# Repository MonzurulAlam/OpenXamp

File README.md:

# OpenExoAmp
Bio-signal Amplifier

### OBJECTIVES:
<P align="justify"> The objective of this project is to develop a bio-signal amplifier for sensing physiological signals.

### DESCRIPTION:
<P align="justify"> Block diagram of an amplifier (OpenExoAmp) for bio-signal amplification and filtering. The amplifier is built with commercially-off-the-shelf components and powered by a pair of batteries. A pre-amplifier section with high common-mode-rejection-ratio (CMRR) is used to differencially pick the bio-signal. If differential input is not required, the inverting input can be shorted with the input reference terminal. The signal is then band-passed filtered and amplified to the desired value by controlling the gain of the amplifier. One can directly use this analog signal or digitised by an analog-t-digital converter (ADC) and a a microcontroller (MCU). The digitised signal can be transfered to a computer via serial network (USB). Note that many MCU boards have built-in ADC and USB interfaces that can be used for the ditisation of the amplified bio-signal. 

### DISCLAIMER:
<P align="justify"> The design is offered as it is. Although it has been regorously tested with utmost care and to the best of my knowledge, I do not provide any warranty in any aspect.

### WARNING:
- The design is intended stricktly for research and education purposes.
- The stimulator is not approved for human or animal use without receving prior approval from a local ethics committee such as Institutional Review Board.

### LICENSE:
##### Documentation licensed under the Creative Commons Attribution Share Alike 4.0 International License

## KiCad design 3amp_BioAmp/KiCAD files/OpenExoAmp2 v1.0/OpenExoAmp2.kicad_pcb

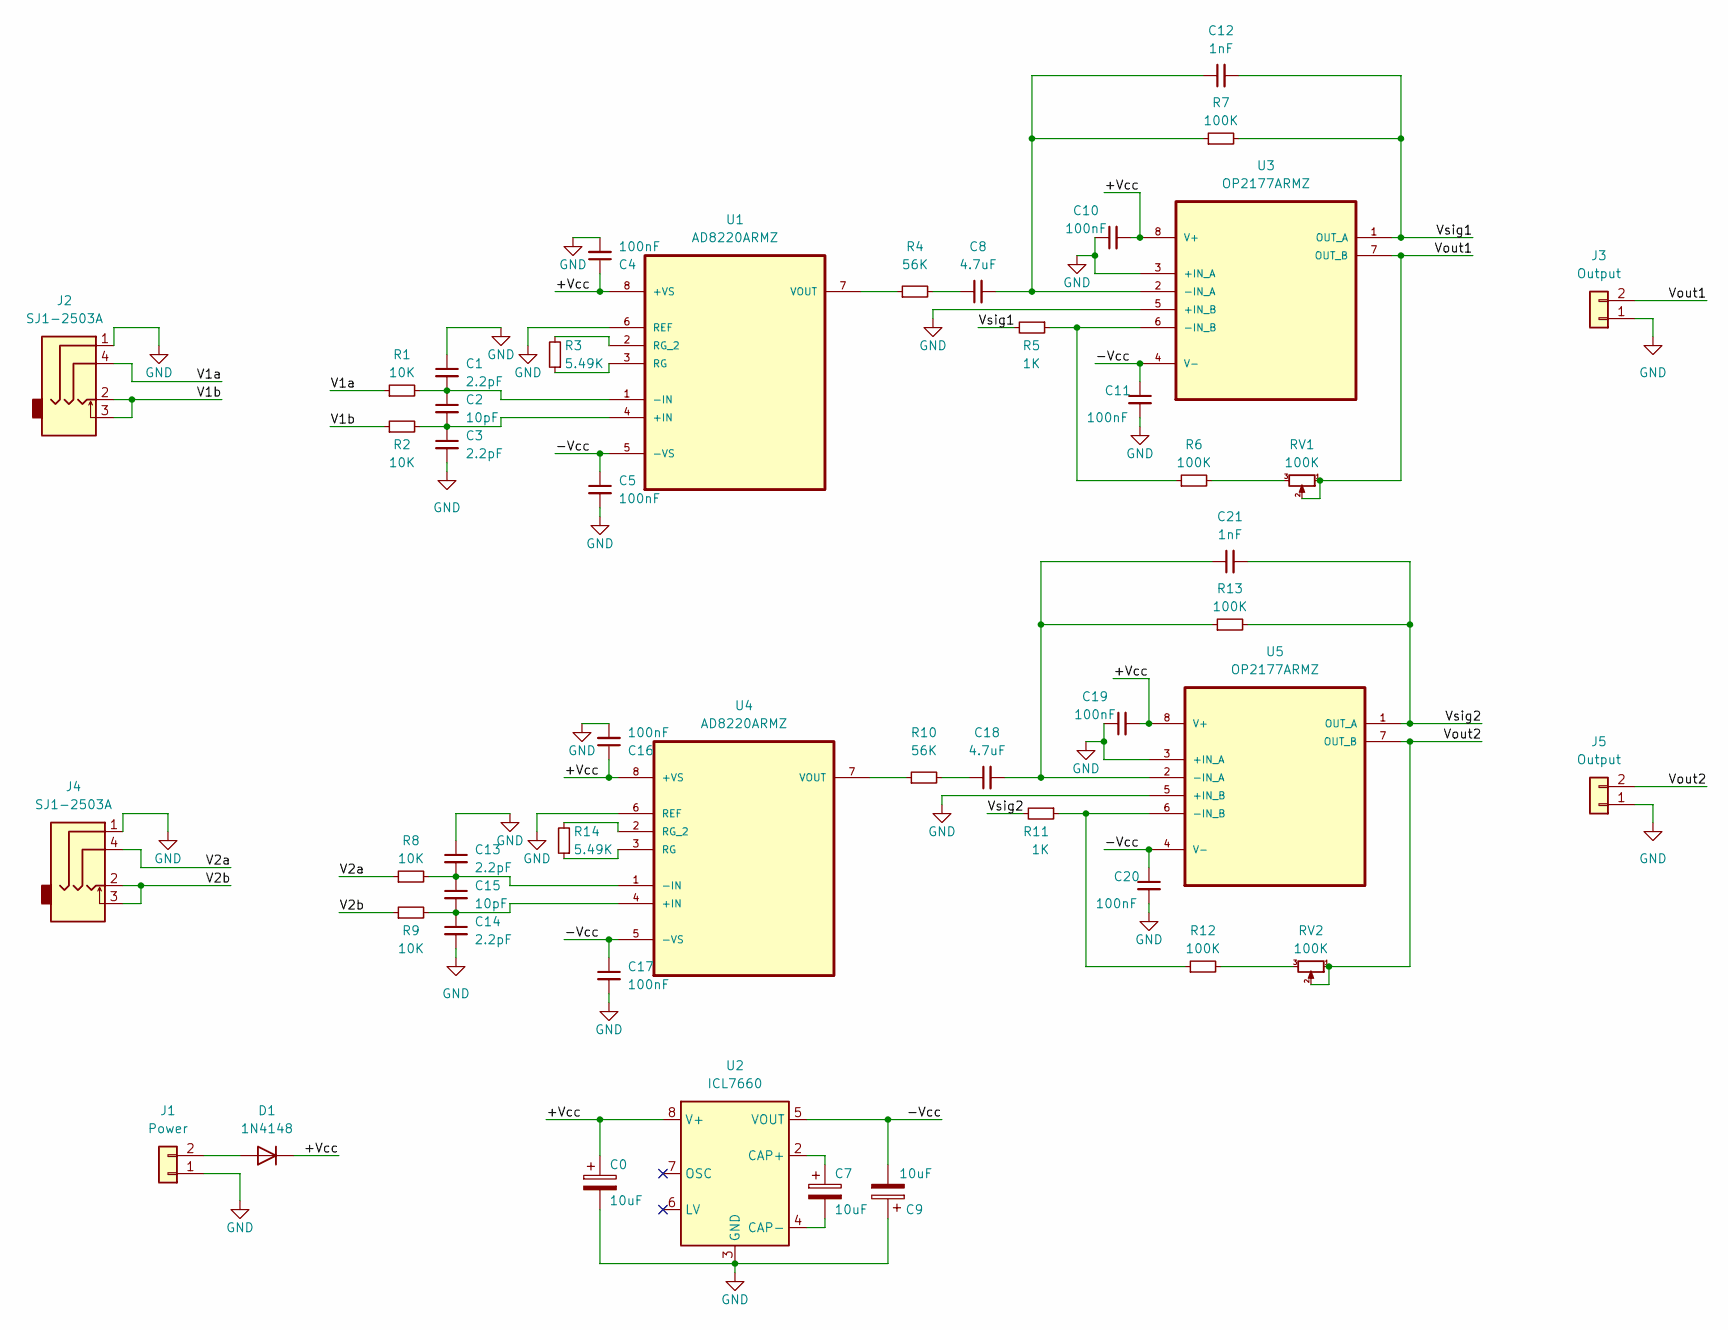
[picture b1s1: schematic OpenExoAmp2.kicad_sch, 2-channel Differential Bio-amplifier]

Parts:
C0, C7, C9: 10uF; C_1206_3216Metric
C1, C3, C13, C14: 2.2pF; C_0603_1608Metric
C2, C15: 10pF; C_0603_1608Metric
C4, C5, C10, C11, C16, C17, C19, C20: 100nF; C_0603_1608Metric
C8, C18: 4.7uF; C_0603_1608Metric
C12, C21: 1nF; C_0603_1608Metric
D1: 1N4148; D_SOD-123
J1: Power; JST_PH_B2B-PH-K_1x02_P2.00mm_Vertical
J2, J4: SJ1-2503A; CUI_SJ1-2503A
J3, J5: Output; PinHeader_1x02_P2.54mm_Vertical
R1, R2, R8, R9: 10K; R_0603_1608Metric
R3, R14: 5.49K; R_0603_1608Metric
R4, R10: 56K; R_0603_1608Metric
R5, R11: 1K; R_0603_1608Metric
R6, R7, R12, R13: 100K; R_0603_1608Metric
RV1, RV2: 100K; TRIM_TC33X-2-104E
U1, U4: AD8220ARMZ; MSOP-8_3x3mm_P0.65mm; MPN AD8220ARMZ
U2: ICL7660; SOIC-8_3.9x4.9mm_P1.27mm
U3, U5: OP2177ARMZ; MSOP-8_3x3mm_P0.65mm; MPN OP2177ARMZ

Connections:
/+Vcc: C0.1, C4.1, C10.2, C16.1, C19.2, D1.1 (K), U1.8 (+VS), U2.8 (V+), U3.8 (V+), U4.8 (+VS), U5.8 (V+)
/-Vcc: C5.1, C9.2, C11.1, C17.1, C20.1, U1.5 (-VS), U2.5 (VOUT), U3.4 (V-), U4.5 (-VS), U5.4 (V-)
/V1a: J2.4, R1.1
/V1b: J2.2, J2.3, R2.1
/V2a: J4.4, R8.1
/V2b: J4.2, J4.3, R9.1
/Vout1: J3.2, RV1.1, RV1.2, U3.7 (OUT_B)
/Vout2: J5.2, RV2.1, RV2.2, U5.7 (OUT_B)
/Vsig1: C12.2, R5.2, R7.2, U3.1 (OUT_A)
/Vsig2: C21.2, R11.2, R13.2, U5.1 (OUT_A)
GND: C0.2, C1.1, C3.2, C4.2, C5.2, C9.1, C10.1, C11.2, C13.1, C14.2, C16.2, C17.2, C19.1, C20.2, J1.1, J2.1, J3.1, J4.1, J5.1, U1.6 (REF), U2.3 (GND), U3.3 (+IN_A), U3.5 (+IN_B), U4.6 (REF), U5.3 (+IN_A), U5.5 (+IN_B)
unnamed: C1.2, C2.1, R1.2, U1.1 (-IN)
unnamed: C2.2, C3.1, R2.2, U1.4 (+IN)
unnamed: C7.1, U2.2 (CAP+)
unnamed: C7.2, U2.4 (CAP-)
unnamed: C8.1, R4.2
unnamed: C8.2, C12.1, R7.1, U3.2 (-IN_A)
unnamed: C13.2, C15.1, R8.2, U4.1 (-IN)
unnamed: C14.1, C15.2, R9.2, U4.4 (+IN)
unnamed: C18.1, R10.2
unnamed: C18.2, C21.1, R13.1, U5.2 (-IN_A)
unnamed: D1.2 (A), J1.2
unnamed: R3.1, U1.3 (RG)
unnamed: R3.2, U1.2 (RG_2)
unnamed: R4.1, U1.7 (VOUT)
unnamed: R5.1, R6.1, U3.6 (-IN_B)
unnamed: R6.2, RV1.3
unnamed: R10.1, U4.7 (VOUT)
unnamed: R11.1, R12.1, U5.6 (-IN_B)
unnamed: R12.2, RV2.3
unnamed: R14.1, U4.3 (RG)
unnamed: R14.2, U4.2 (RG_2)

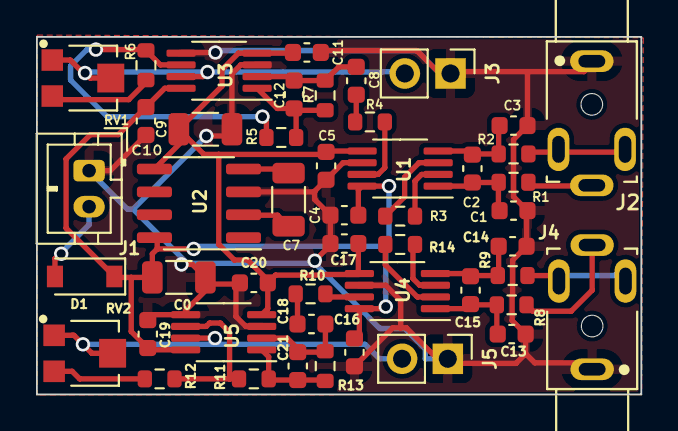
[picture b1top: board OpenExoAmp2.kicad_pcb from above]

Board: 2 copper layers, 33.6 x 19.9 mm, 48 parts (0 on the bottom side), 32 nets.
